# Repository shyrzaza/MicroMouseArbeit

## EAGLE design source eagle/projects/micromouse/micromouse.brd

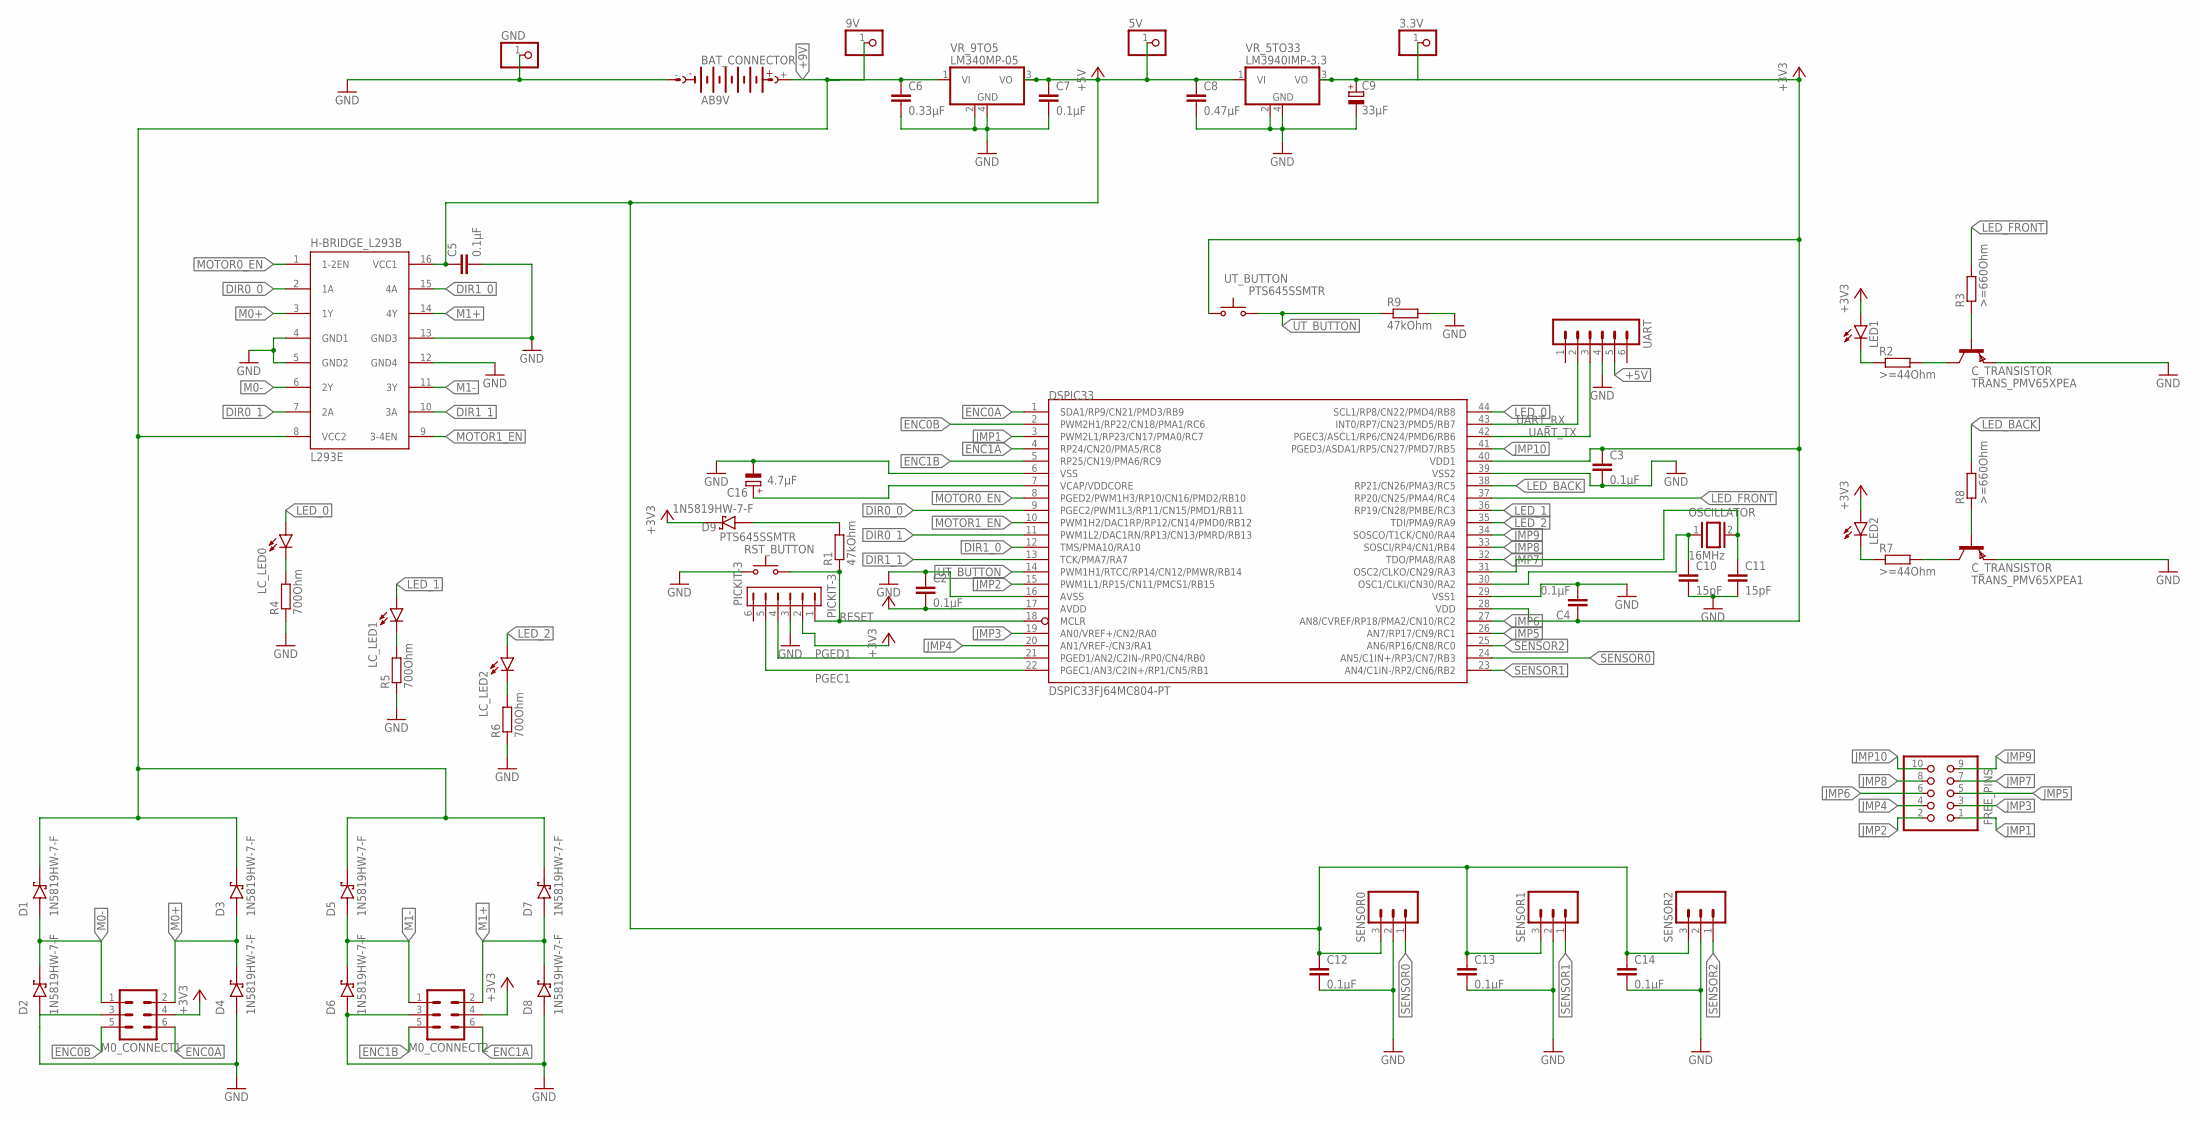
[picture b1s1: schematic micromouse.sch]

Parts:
3.3V, 5V, 9V: PINHD-1X1; 1X01
BAT_CONNECTOR: AB9V
C2, C3, C4, C5, C7, C12, C13, C14: 0.1µF; C0805
C6: 0.33µF; C0805
C8: 0.47µF; C0805
C9: 33µF; D/7343-31W
C10, C11: 15pF; C0805
C16: 4.7µF; CT3528
D1, D2, D3, D4, D5, D6, D7, D8, D9: 1N5819HW-7-F; SOD3715X145N
DSPIC33: DSPIC33FJ64MC804-PT; TQFP44
FREE_PINS: PINHD-2X5; 2X05
GND: PINHD-1X1; 1X01
H-BRIDGE_L293B: L293E; DIL16
LC_LED0, LC_LED1, LC_LED2: LED5MM
LED1, LED2: L-1503ID-LED-DLED; L-1503ID-LED
M0_CONNECT1, M0_CONNECT2: MA03-2
OSCILLATOR: 16MHz; QS
PICKIT-3: PICKIT-3; 1X06
R1, R9: 47kOhm; R0805
R2, R7: >=44Ohm; R0805
R3, R8: >=660Ohm; R0805
R4, R5, R6: 700Ohm; R0805
RST_BUTTON: PTS645SSMTR; PTS645-SMD
SENSOR0, SENSOR1, SENSOR2: M03; 03P
TRANS_PMV65XPEA, TRANS_PMV65XPEA1: C_TRANSISTOR; SOT23
UART: MA06-1
UT_BUTTON: PTS645SSMTR; PTS645-SMD
VR_5TO33: LM3940IMP-3.3; SOT223
VR_9TO5: LM340MP-05; SOT223

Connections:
+3V3: 3.3V.1, C2.2, C3.1, C4.1, C9.+, D9.C (K), DSPIC33.17 (AVDD), DSPIC33.28 (VDD), DSPIC33.40 (VDD1), LED1.A, LED2.A, M0_CONNECT1.4, M0_CONNECT2.4, PICKIT-3.2 (VDD), UT_BUTTON.1, UT_BUTTON.2, VR_5TO33.3 (VO)
+5V: 5V.1, C5.1, C7.1, C8.1, C12.1, C13.1, C14.1, H-BRIDGE_L293B.16 (VCC1), SENSOR0.3, SENSOR1.3, SENSOR2.3, UART.5, VR_5TO33.1 (VI), VR_9TO5.3 (VO)
+9V: 9V.1, BAT_CONNECTOR.+, C6.1, D1.C (K), D3.C (K), D5.C (K), D7.C (K), H-BRIDGE_L293B.8 (VCC2), VR_9TO5.1 (VI)
DIR0_0: DSPIC33.9 (PGEC2/PWM1L3/RP11/CN15/PMD1/RB11), H-BRIDGE_L293B.2 (1A)
DIR0_1: DSPIC33.11 (PWM1L2/DAC1RN/RP13/CN13/PMRD/RB13), H-BRIDGE_L293B.7 (2A)
DIR1_0: DSPIC33.12 (TMS/PMA10/RA10), H-BRIDGE_L293B.15 (4A)
DIR1_1: DSPIC33.13 (TCK/PMA7/RA7), H-BRIDGE_L293B.10 (3A)
ENC0A: DSPIC33.1 (SDA1/RP9/CN21/PMD3/RB9), M0_CONNECT1.6
ENC0B: DSPIC33.2 (PWM2H1/RP22/CN18/PMA1/RC6), M0_CONNECT1.5
ENC1A: DSPIC33.4 (RP24/CN20/PMA5/RC8), M0_CONNECT2.6
ENC1B: DSPIC33.5 (RP25/CN19/PMA6/RC9), M0_CONNECT2.5
GND: BAT_CONNECTOR.-, C2.1, C3.2, C4.2, C5.2, C6.2, C7.2, C8.2, C9.-, C10.2, C11.2, C12.2, C13.2, C14.2, C16.-, D2.A, D4.A, D6.A, D8.A, DSPIC33.6 (VSS), DSPIC33.16 (AVSS), DSPIC33.29 (VSS1), DSPIC33.39 (VSS2), GND.1, H-BRIDGE_L293B.4 (GND1), H-BRIDGE_L293B.5 (GND2), H-BRIDGE_L293B.12 (GND4), H-BRIDGE_L293B.13 (GND3), M0_CONNECT1.3, M0_CONNECT2.3, PICKIT-3.3 (VSS), R4.1, R5.1, R6.1, R9.2, RST_BUTTON.1, RST_BUTTON.2, SENSOR0.2, SENSOR1.2, SENSOR2.2, TRANS_PMV65XPEA.2 (E), TRANS_PMV65XPEA1.2 (E), UART.4, VR_5TO33.2 (GND1), VR_5TO33.4 (GND), VR_9TO5.2 (GND1), VR_9TO5.4 (GND)
JMP1: DSPIC33.3 (PWM2L1/RP23/CN17/PMA0/RC7), FREE_PINS.1
JMP2: DSPIC33.15 (PWM1L1/RP15/CN11/PMCS1/RB15), FREE_PINS.2
JMP3: DSPIC33.19 (AN0/VREF+/CN2/RA0), FREE_PINS.3
JMP4: DSPIC33.20 (AN1/VREF-/CN3/RA1), FREE_PINS.4
JMP5: DSPIC33.26 (AN7/RP17/CN9/RC1), FREE_PINS.5
JMP6: DSPIC33.27 (AN8/CVREF/RP18/PMA2/CN10/RC2), FREE_PINS.6
JMP7: DSPIC33.32 (TDO/PMA8/RA8), FREE_PINS.7
JMP8: DSPIC33.33 (SOSCI/RP4/CN1/RB4), FREE_PINS.8
JMP9: DSPIC33.34 (SOSCO/T1CK/CN0/RA4), FREE_PINS.9
JMP10: DSPIC33.41 (PGED3/ASDA1/RP5/CN27/PMD7/RB5), FREE_PINS.10
LED_0: DSPIC33.44 (SCL1/RP8/CN22/PMD4/RB8), LC_LED0.A
LED_1: DSPIC33.36 (RP19/CN28/PMBE/RC3), LC_LED1.A
LED_2: DSPIC33.35 (TDI/PMA9/RA9), LC_LED2.A
LED_BACK: DSPIC33.38 (RP21/CN26/PMA3/RC5), R8.2
LED_FRONT: DSPIC33.37 (RP20/CN25/PMA4/RC4), R3.2
M0+: D3.A, D4.C (K), H-BRIDGE_L293B.3 (1Y), M0_CONNECT1.2
M0-: D1.A, D2.C (K), H-BRIDGE_L293B.6 (2Y), M0_CONNECT1.1
M1+: D7.A, D8.C (K), H-BRIDGE_L293B.14 (4Y), M0_CONNECT2.2
M1-: D5.A, D6.C (K), H-BRIDGE_L293B.11 (3Y), M0_CONNECT2.1
MOTOR0_EN: DSPIC33.8 (PGED2/PWM1H3/RP10/CN16/PMD2/RB10), H-BRIDGE_L293B.1 (1-2EN)
MOTOR1_EN: DSPIC33.10 (PWM1H2/DAC1RP/RP12/CN14/PMD0/RB12), H-BRIDGE_L293B.9 (3-4EN)
unnamed: LED1.K (C), R2.1
unnamed: D9.A, R1.2
unnamed: LC_LED1.K (C), R5.2
unnamed: LC_LED2.K (C), R6.2
unnamed: LC_LED0.K (C), R4.2
unnamed: R2.2, TRANS_PMV65XPEA.3 (C)
unnamed: R3.1, TRANS_PMV65XPEA.1 (B)
unnamed: LED2.K (C), R7.1
unnamed: R7.2, TRANS_PMV65XPEA1.3 (C)
unnamed: R8.1, TRANS_PMV65XPEA1.1 (B)
OSC1: C10.1, DSPIC33.30 (OSC1/CLKI/CN30/RA2), OSCILLATOR.1
OSC2: C11.1, DSPIC33.31 (OSC2/CLKO/CN29/RA3), OSCILLATOR.2
PGEC1: DSPIC33.22 (PGEC1/AN3/C2IN+/RP1/CN5/RB1), PICKIT-3.5 (PGC)
PGED1: DSPIC33.21 (PGED1/AN2/C2IN-/RP0/CN4/RB0), PICKIT-3.4 (PGD)
RESET: DSPIC33.18 (MCLR), PICKIT-3.1 (MCLR), R1.1, RST_BUTTON.3 (S), RST_BUTTON.4 (S)
SENSOR0: DSPIC33.24 (AN5/C1IN+/RP3/CN7/RB3), SENSOR0.1
SENSOR1: DSPIC33.23 (AN4/C1IN-/RP2/CN6/RB2), SENSOR1.1
SENSOR2: DSPIC33.25 (AN6/RP16/CN8/RC0), SENSOR2.1
UART_RX: DSPIC33.43 (INT0/RP7/CN23/PMD5/RB7), UART.2
UART_TX: DSPIC33.42 (PGEC3/ASCL1/RP6/CN24/PMD6/RB6), UART.3
UT_BUTTON: DSPIC33.14 (PWM1H1/RTCC/RP14/CN12/PMWR/RB14), R9.1, UT_BUTTON.3 (S), UT_BUTTON.4 (S)
VCAP/VDDCORE: C16.+, DSPIC33.7 (VCAP/VDDCORE)

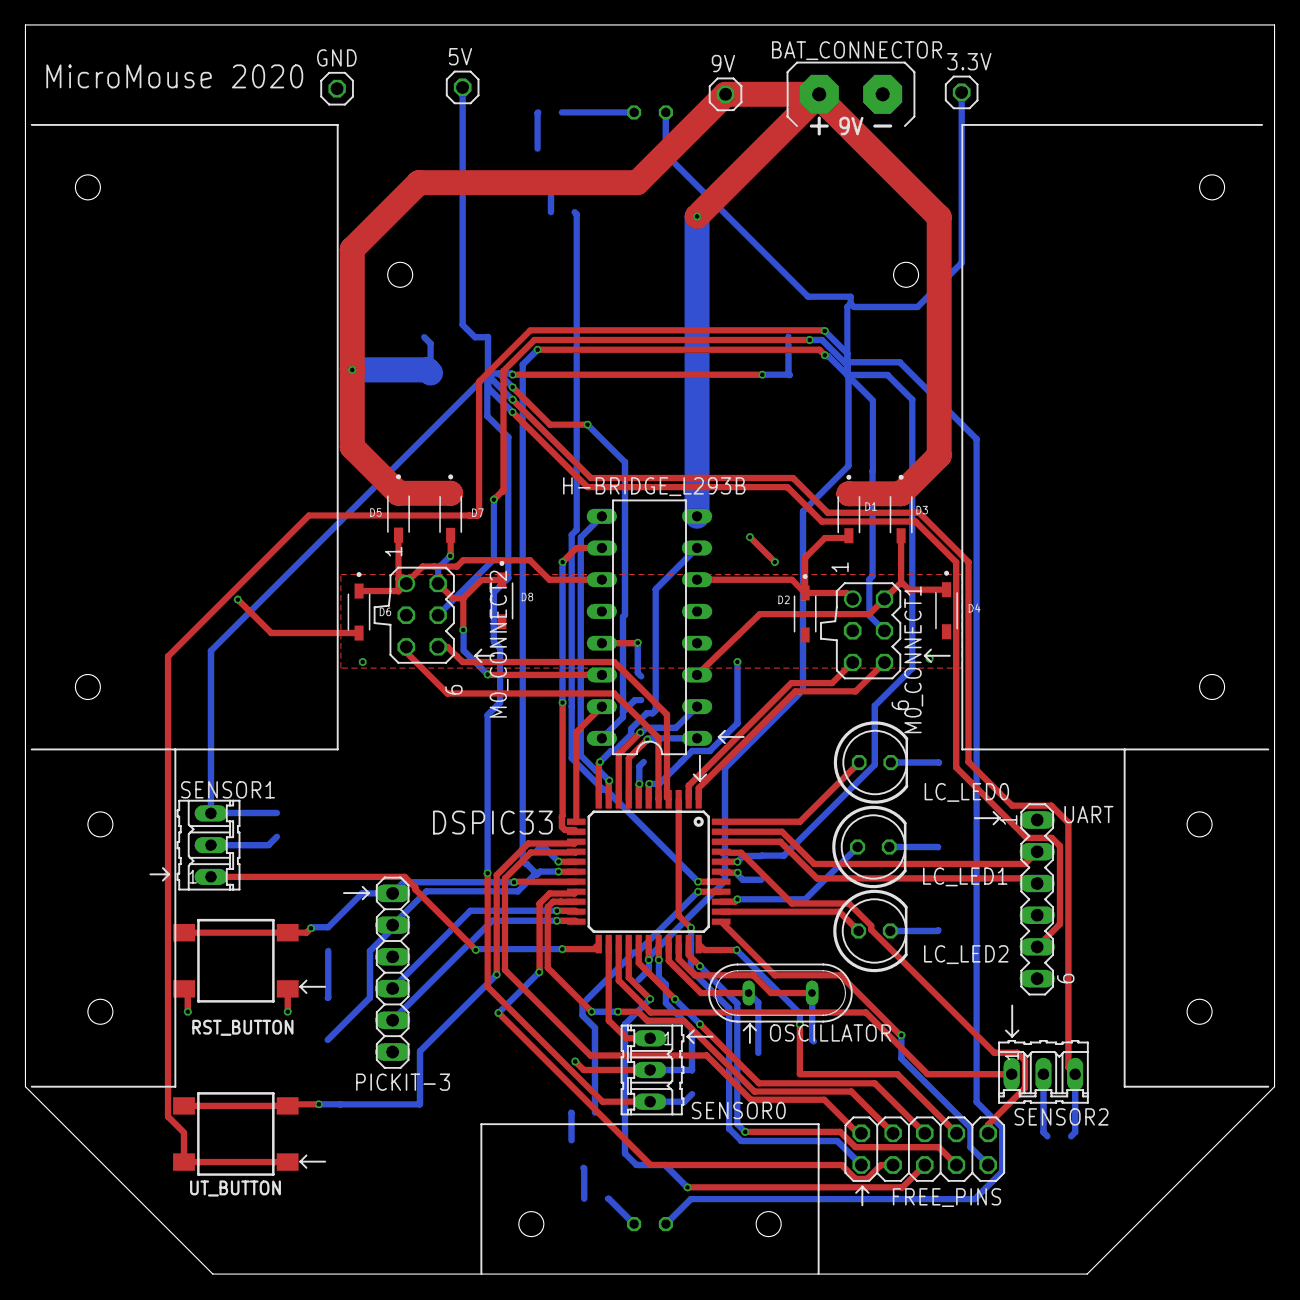
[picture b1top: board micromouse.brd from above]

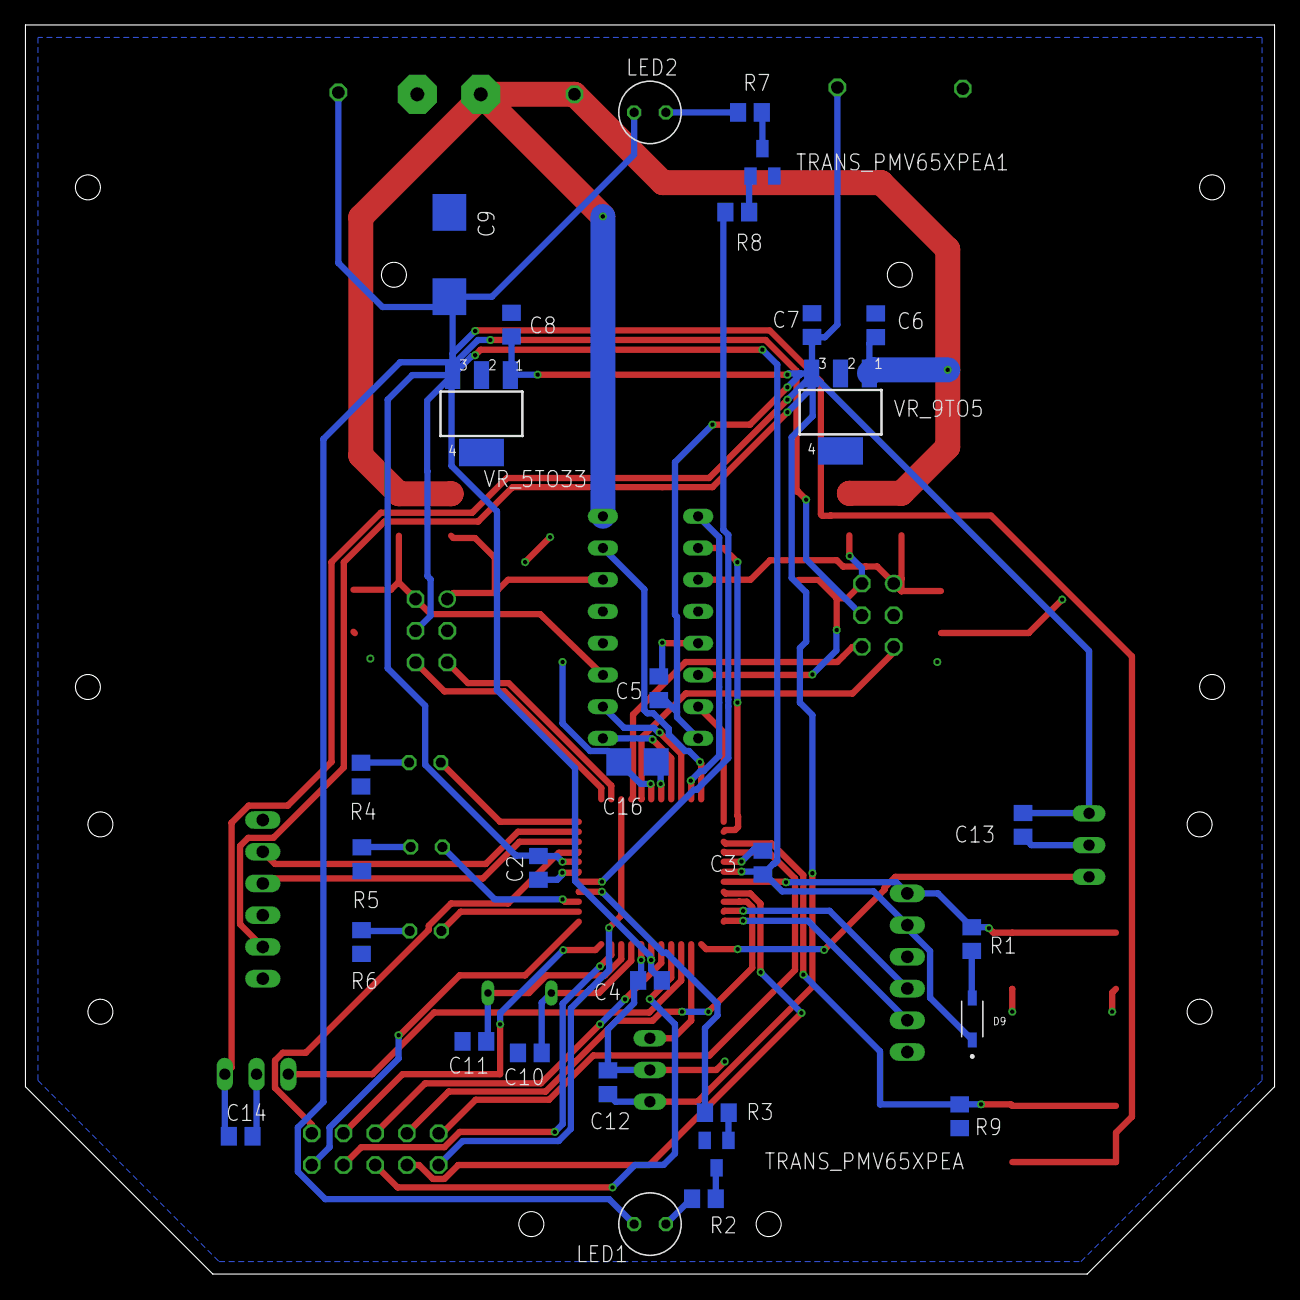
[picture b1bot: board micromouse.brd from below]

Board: 2 copper layers, 100.0 x 100.0 mm, 59 parts (30 on the bottom side), 55 nets.

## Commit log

2020-07-21 pythondebugger
2020-07-28 Setup
2020-07-28 laptop init
2020-07-28 better board design, capacitor missing
2020-08-12 Matlab logging
2020-08-12 Board fertig, vllt noch silk?
2020-08-12 C files
2020-08-12 Teilliste
2020-09-17 motor and sensor mount files added
2020-09-17 small changes to board and matlab files
2020-11-19 updated ld voltage regulator 3.3v

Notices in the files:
parts and their libraries:
switch-ck: Copyright (C) 2011, Bob Starr
